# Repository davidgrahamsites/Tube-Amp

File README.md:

# Renegade Tube Amp

KiCad engineering project for an original six-tube amplifier with solid-state spring reverb.

Two separate builds are tracked in Git:

| Branch | Build |
|---|---|
| `electric-guitar-amp` | Original electric-guitar amplifier and spring reverb |
| `acoustic-guitar-amp` | Acoustic-specific input buffer and speaker/crossover development |

For the acoustic build, start with [ACOUSTIC_HANDOFF.md](ACOUSTIC_HANDOFF.md). Read [BUILD_VARIANT.md](BUILD_VARIANT.md) to identify the checked-out build. Read [PROJECT_STATUS.md](PROJECT_STATUS.md) for actual completed checks and unresolved work. Neither branch is a construction release.

## Project map

- [Workspace contract](CONTEXT.md)
- [Current material catalog](brain/catalog/WORKSPACE.md)
- [Requirements and handoff](Renegade_Codex_Handoff.md)
- [Selected component BOM](engineering/component-selection/selected-engineering-bom.csv)
- [Current 600R-1 schematic](engineering/whole-amp/reverb-600/cad/Renegade_220V_Reverb.kicad_sch)
- [Four-board engineering draft](engineering/whole-amp/pcb-measured-r/CONTEXT.md)
- [Measured-resistance simulation and PCB review](engineering/whole-amp/reverb-600/review/measured-resistance-results-2026-11-20.md)
- [Received-cabinet fit evidence](engineering/whole-amp/mechanical/CONTEXT.md)

Historical designs and failed/limited simulations are retained as evidence. Native KiCad factories marked with overwrite guards must not be rerun over later manual edits. Supplier PDFs, source artwork and third-party models retain their original ownership and licensing.

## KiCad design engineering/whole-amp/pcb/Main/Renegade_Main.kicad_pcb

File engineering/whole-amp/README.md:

# Whole-amplifier PCB development — v0.5

**Development only. Not build-ready or released for fabrication.** The original amplifier and v0.4 files are preserved. This revision extends PCB coverage to Main, Power and Control alongside the existing Reverb board. Socket-local grid/screen resistors and cathode sense resistors remain directly at the valve sockets; transformers, valves, panel parts and protective earth remain chassis mounted.

## Current artifacts
- `integrated/Renegade_220V_Reverb.kicad_sch` and `integrated/Renegade-v0.5-development.pdf`: separate integrated development schematic; pin partitions match v0.4.
- `bom-development.csv` and `build-plan.md`: assembly register and staged build/test plan, with unresolved purchase parts explicitly marked.
- `harness-terminals.csv`: terminal-to-net list from saved boards.
- `board-plan.json`: component-to-assembly register, provisional envelopes and footprints.
- `pcb/Main`, `pcb/Power`, `pcb/Control`: editable native board projects and assembly connectivity schematics. All three are routed, with zero native DRC, unconnected and schematic parity issues in the final saved checks. The preserved Reverb project is included in `pcb/Reverb`. This is a development revision, not a fabrication release.
- `validation/pin-partition.json`: native schematic-to-board pad/net mapping checks.
- `validation/*-drc.json`: latest native reports; failures remain visible.
- `simulation/`: reproducible full signal-path and supply stress fixtures, results, models and failure logs.
- `evidence/`: manufacturer documents and supplier contact record.

## Supplier inquiry
Sent and verified in Mail Sent on November 11 at 06:22 America/Los_Angeles, from the user-selected admin@goodgaryapps.com to mable@mableaudio.com. Cabinet choice unchanged. Internal dimensions, Shanghai availability/quote and exact spring-tank documentation requested. No order, attachments or design upload.

## Engineering limits still to close
1. Engineering review of all board placements, return paths, decoupling, heat and coupling. Main/Power were regrouped by circuit section; Control in particular still needs decoupling/thermal placement review. Routing completion is not an analog layout review.
2. Repeat native checks after any engineering changes. Main/Power/Control currently have clean assembly ERC and PCB DRC/parity reports; the integrated schematic retains the documented PE/GND alias warning. Board previews were rendered and inspected.
3. Exact remaining parts, HV standby and fuse coordination, isolated LV transformer and heatsink selection; procurement evidence in China.
4. Full amplifier model qualification: generic valve/ideal magnetics assumptions, overdrive screen stress, solid-state dry-path headroom and transient convergence.
5. Supplier-confirmed internal cabinet geometry and actual component envelopes before chassis/panel fabrication drawings. Current board sizes are provisional and not fit claims.
6. Reviewed grounding, harness, test/bring-up plan and subsequent physical fit/thermal/energized measurements.

No Gerbers are released from this revision. The previous reverb-only package is also an engineering draft, not authorization to manufacture the complete amplifier.

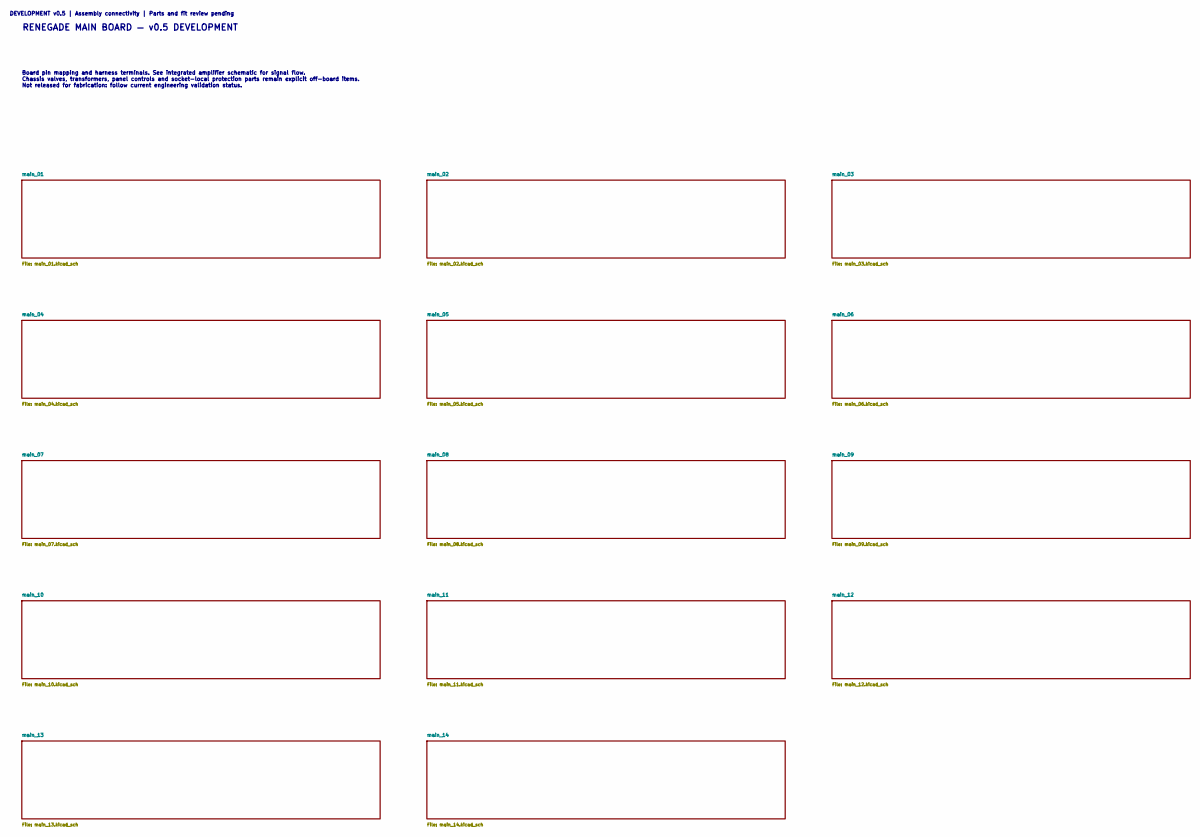
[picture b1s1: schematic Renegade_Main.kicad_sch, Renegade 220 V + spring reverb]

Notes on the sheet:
RENEGADE MAIN BOARD — v0.5 DEVELOPMENT
Board pin mapping and harness terminals. See integrated amplifier schematic for signal flow. Chassis valves, transformers, panel controls and socket-local protection parts remain explicit off-board items. Not released for fabrication: follow current engineering validation status.
DEVELOPMENT v0.5 | Assembly connectivity | Parts and fit review pending

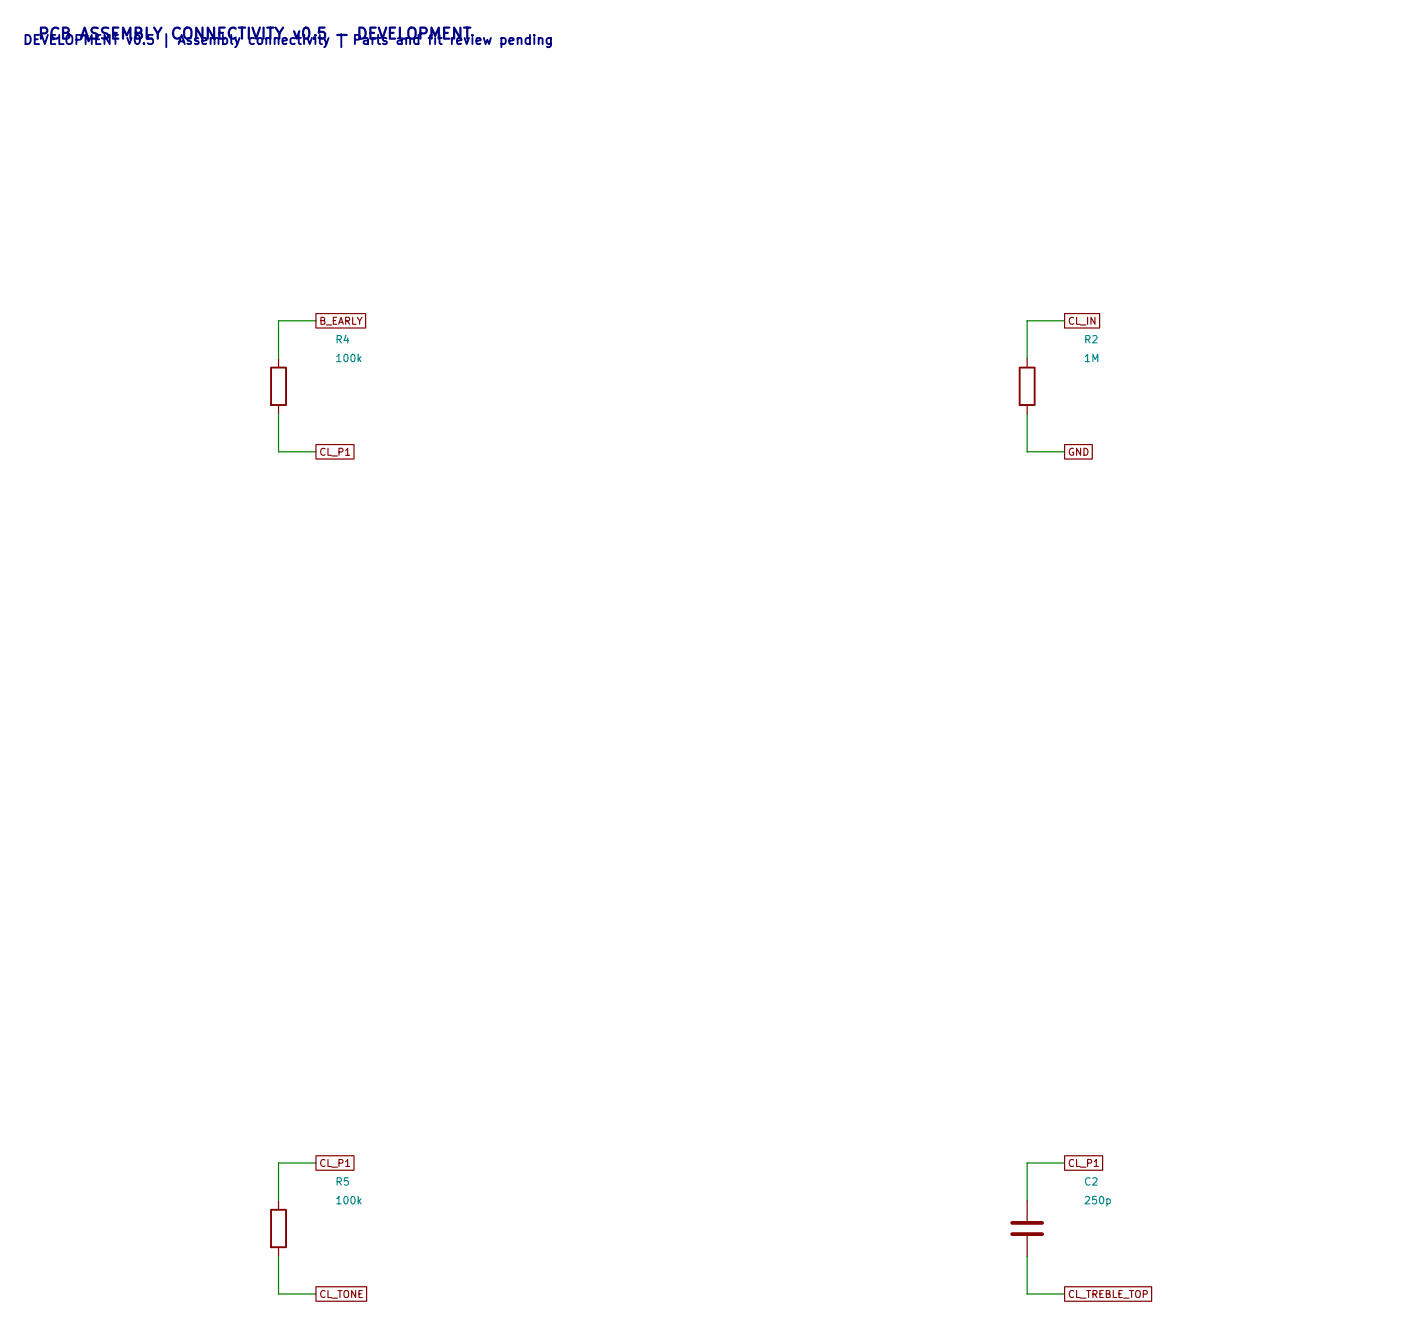
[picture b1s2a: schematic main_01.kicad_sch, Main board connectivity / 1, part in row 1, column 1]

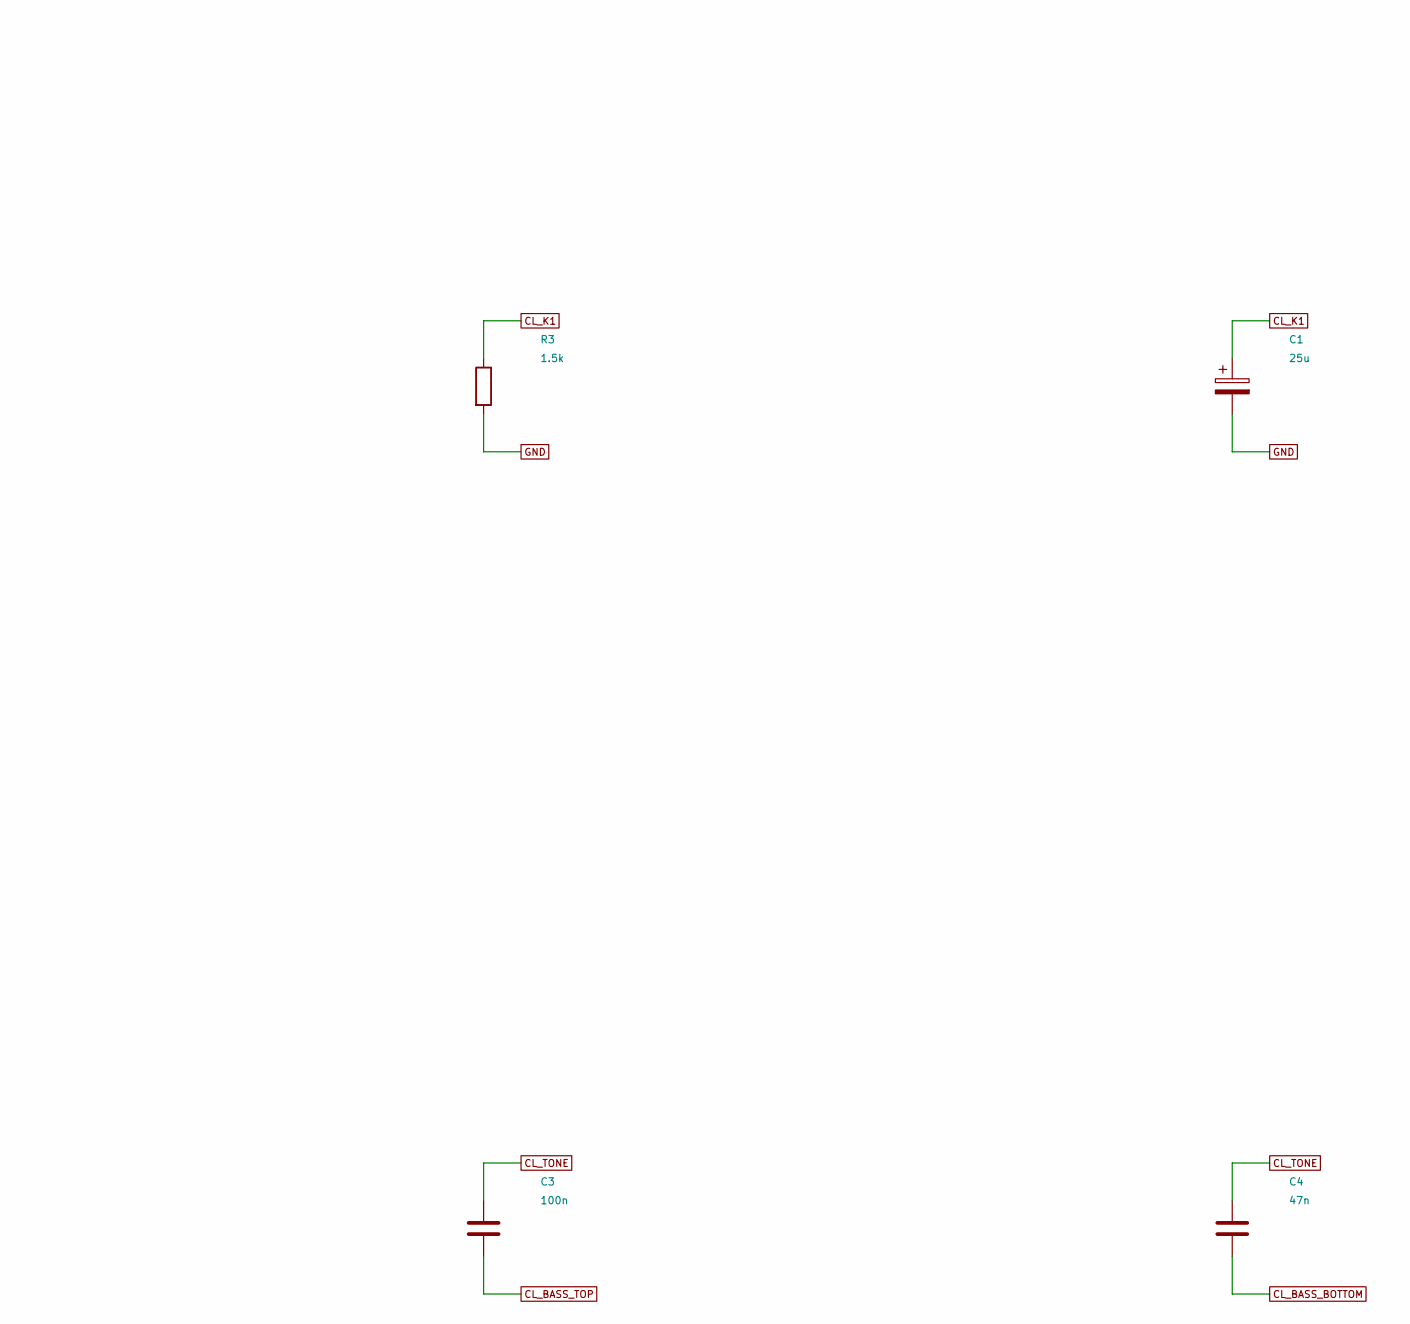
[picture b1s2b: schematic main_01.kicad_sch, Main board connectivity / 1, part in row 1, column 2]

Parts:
C1: 25u; CP_Axial_L25.0mm_D10.0mm_P30.00mm_Horizontal; Rating 50 V
C2: 250p; C_Disc_D7.5mm_W5.0mm_P10.00mm; Rating 630 V film
C3: 100n; C_Rect_L18.0mm_W7.0mm_P15.00mm_FKS3_FKP3; Rating 630 V film
C4: 47n; C_Rect_L18.0mm_W7.0mm_P15.00mm_FKS3_FKP3; Rating 630 V film
R2: 1M; R_Axial_DIN0207_L6.3mm_D2.5mm_P15.24mm_Horizontal; Rating 0.5 W minimum; exact part pending
R3: 1.5k; R_Axial_DIN0207_L6.3mm_D2.5mm_P15.24mm_Horizontal; Rating 0.5 W minimum; exact part pending
R4, R5: 100k; R_Axial_DIN0207_L6.3mm_D2.5mm_P15.24mm_Horizontal; Rating 0.5 W minimum; exact part pending

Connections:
B_EARLY: R4.1; also elsewhere on the board
CL_BASS_BOTTOM: C4.2; also elsewhere on the board
CL_BASS_TOP: C3.2; also elsewhere on the board
CL_IN: R2.1; also elsewhere on the board
CL_K1: C1.1, R3.1; also elsewhere on the board
CL_P1: C2.1, R4.2, R5.1; also elsewhere on the board
CL_TONE: C3.1, C4.1, R5.2
CL_TREBLE_TOP: C2.2; also elsewhere on the board
GND: C1.2, R2.2, R3.2; also elsewhere on the board

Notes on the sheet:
PCB ASSEMBLY CONNECTIVITY v0.5 — DEVELOPMENT
DEVELOPMENT v0.5 | Assembly connectivity | Parts and fit review pending

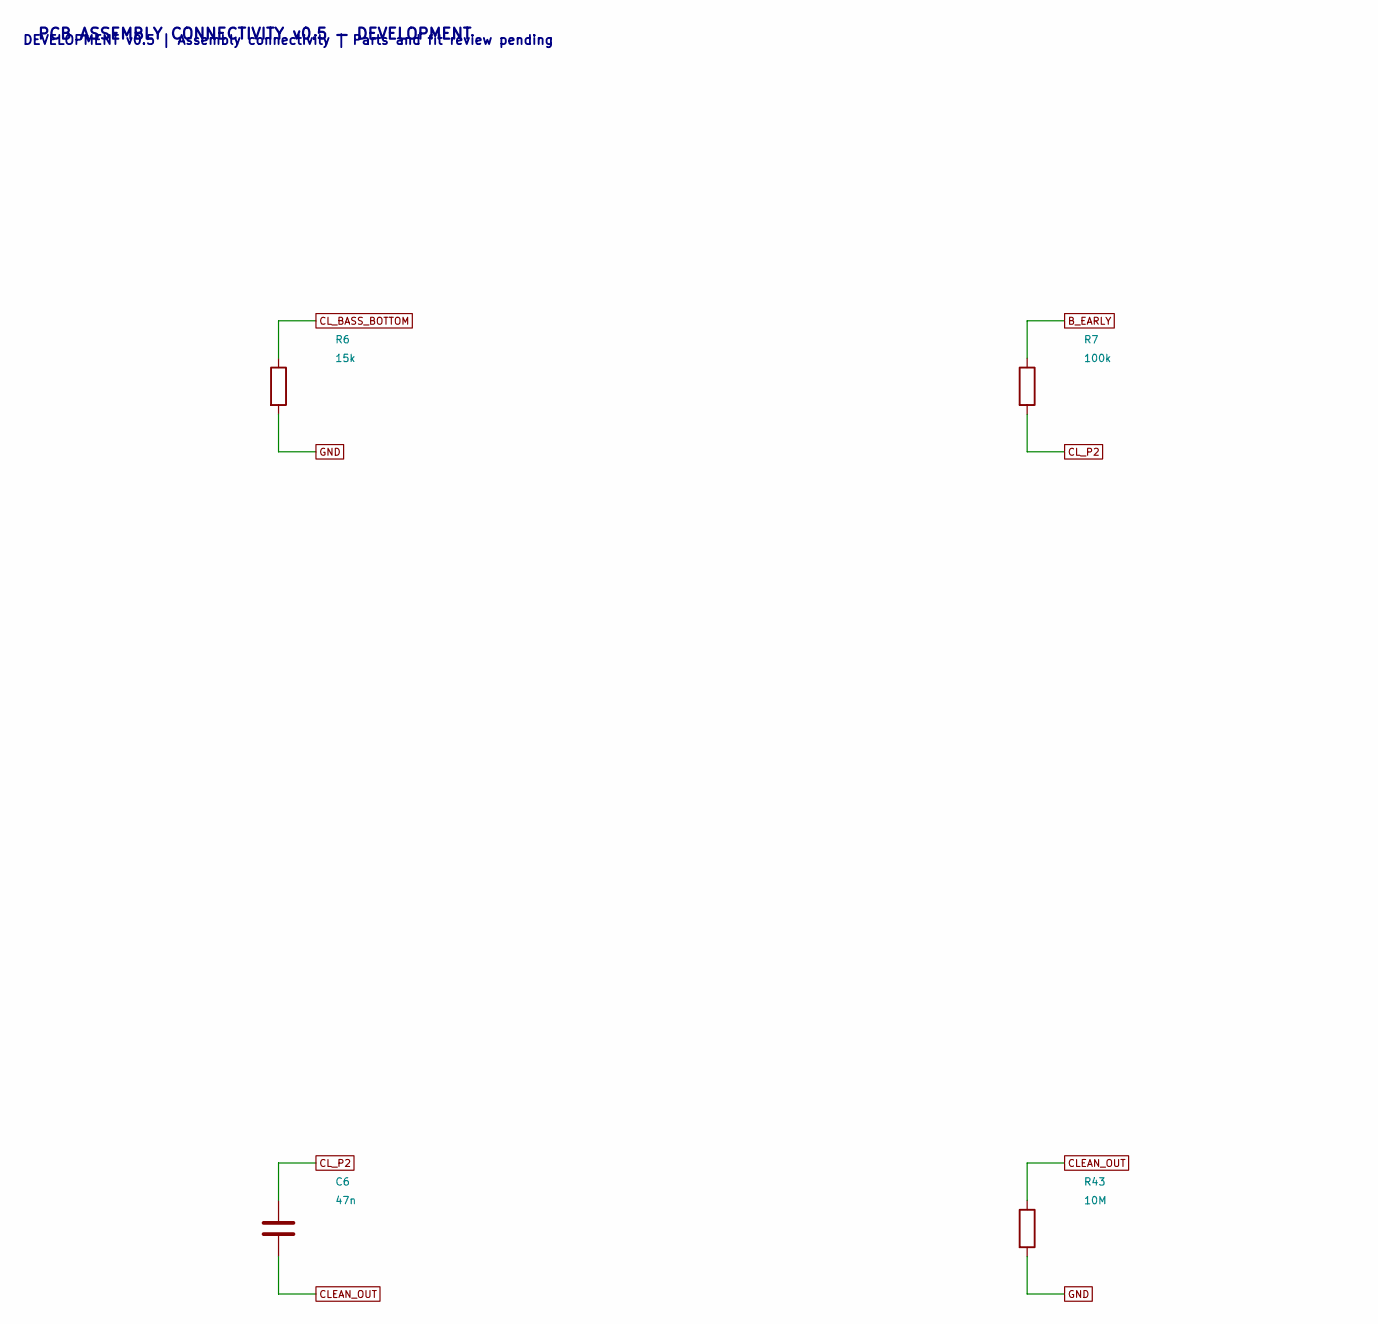
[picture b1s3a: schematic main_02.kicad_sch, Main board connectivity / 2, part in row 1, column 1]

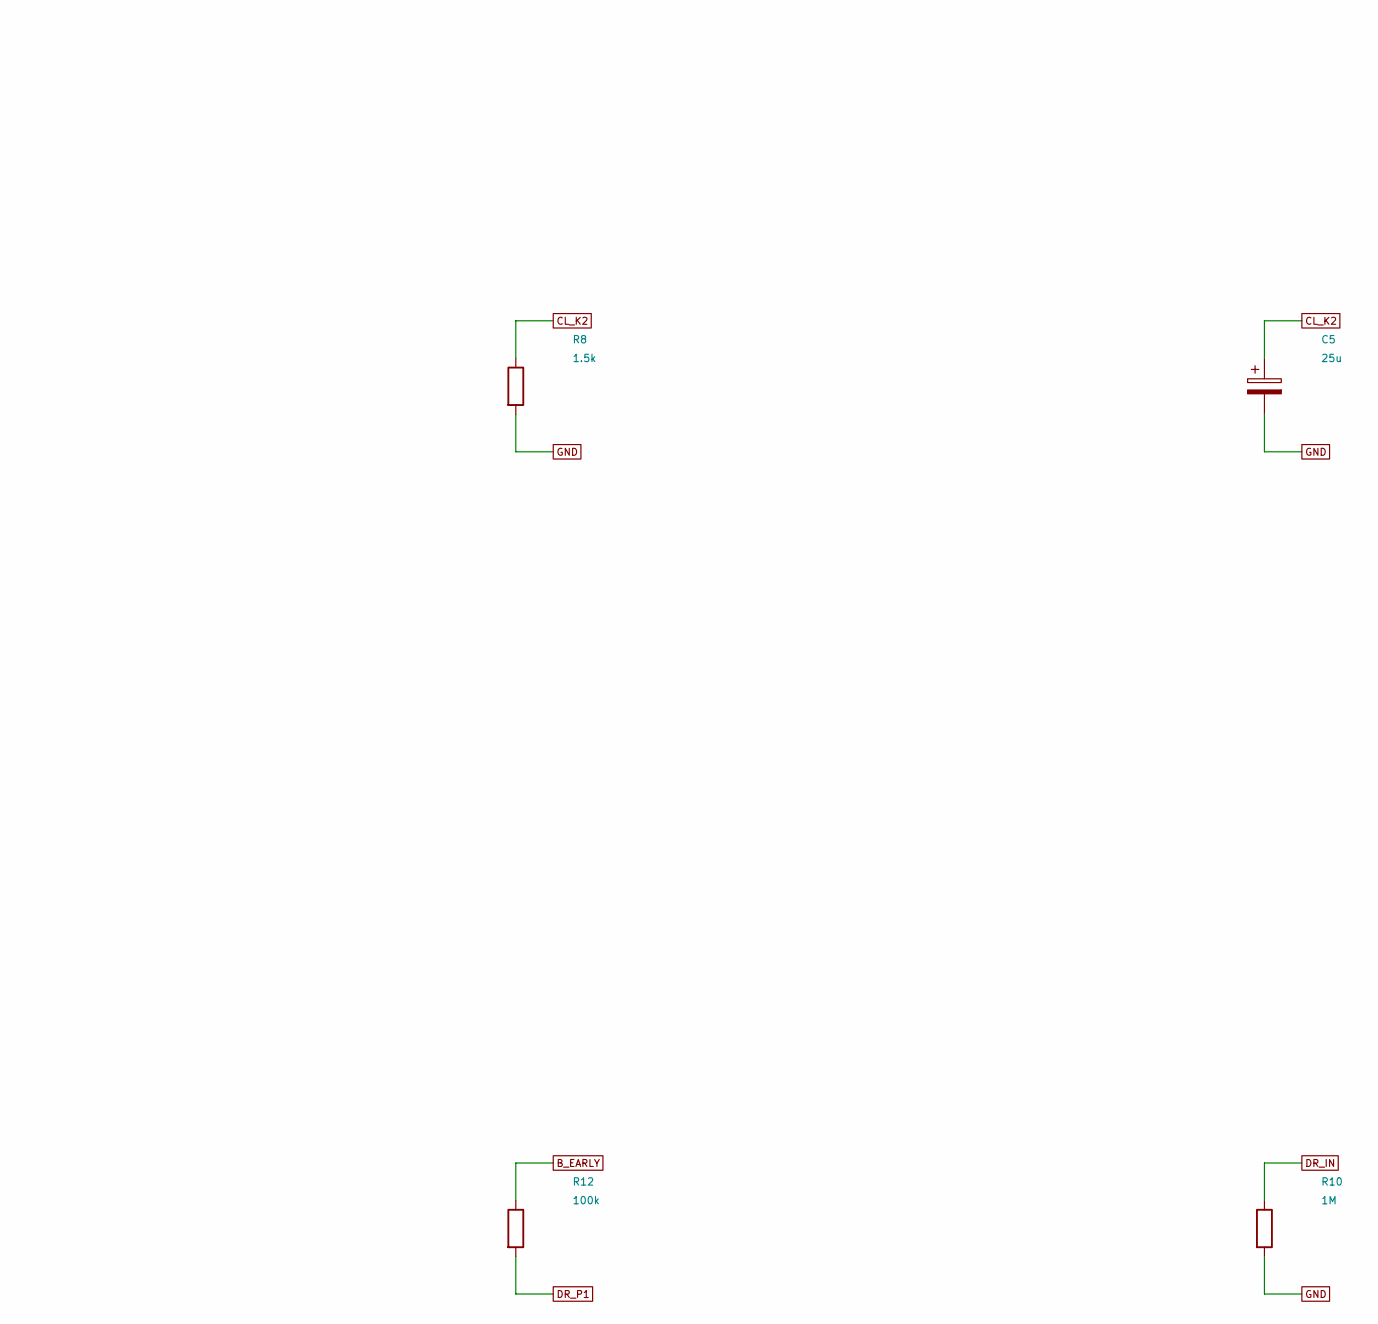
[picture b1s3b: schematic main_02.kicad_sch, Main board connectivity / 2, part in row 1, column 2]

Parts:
C5: 25u; CP_Axial_L25.0mm_D10.0mm_P30.00mm_Horizontal; Rating 50 V
C6: 47n; C_Rect_L18.0mm_W7.0mm_P15.00mm_FKS3_FKP3; Rating 630 V film
R6: 15k; R_Axial_DIN0207_L6.3mm_D2.5mm_P15.24mm_Horizontal; Rating 0.5 W minimum; exact part pending
R7, R12: 100k; R_Axial_DIN0207_L6.3mm_D2.5mm_P15.24mm_Horizontal; Rating 0.5 W minimum; exact part pending
R8: 1.5k; R_Axial_DIN0207_L6.3mm_D2.5mm_P15.24mm_Horizontal; Rating 0.5 W minimum; exact part pending
R10: 1M; R_Axial_DIN0207_L6.3mm_D2.5mm_P15.24mm_Horizontal; Rating 0.5 W minimum; exact part pending
R43: 10M; R_Axial_DIN0207_L6.3mm_D2.5mm_P15.24mm_Horizontal; Rating 0.5 W minimum; exact part pending

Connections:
B_EARLY: R7.1, R12.1; also elsewhere on the board
CLEAN_OUT: C6.2, R43.1; also elsewhere on the board
CL_BASS_BOTTOM: R6.1; also elsewhere on the board
CL_K2: C5.1, R8.1; also elsewhere on the board
CL_P2: C6.1, R7.2; also elsewhere on the board
DR_IN: R10.1; also elsewhere on the board
DR_P1: R12.2; also elsewhere on the board
GND: C5.2, R6.2, R8.2, R10.2, R43.2; also elsewhere on the board

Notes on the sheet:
PCB ASSEMBLY CONNECTIVITY v0.5 — DEVELOPMENT
DEVELOPMENT v0.5 | Assembly connectivity | Parts and fit review pending

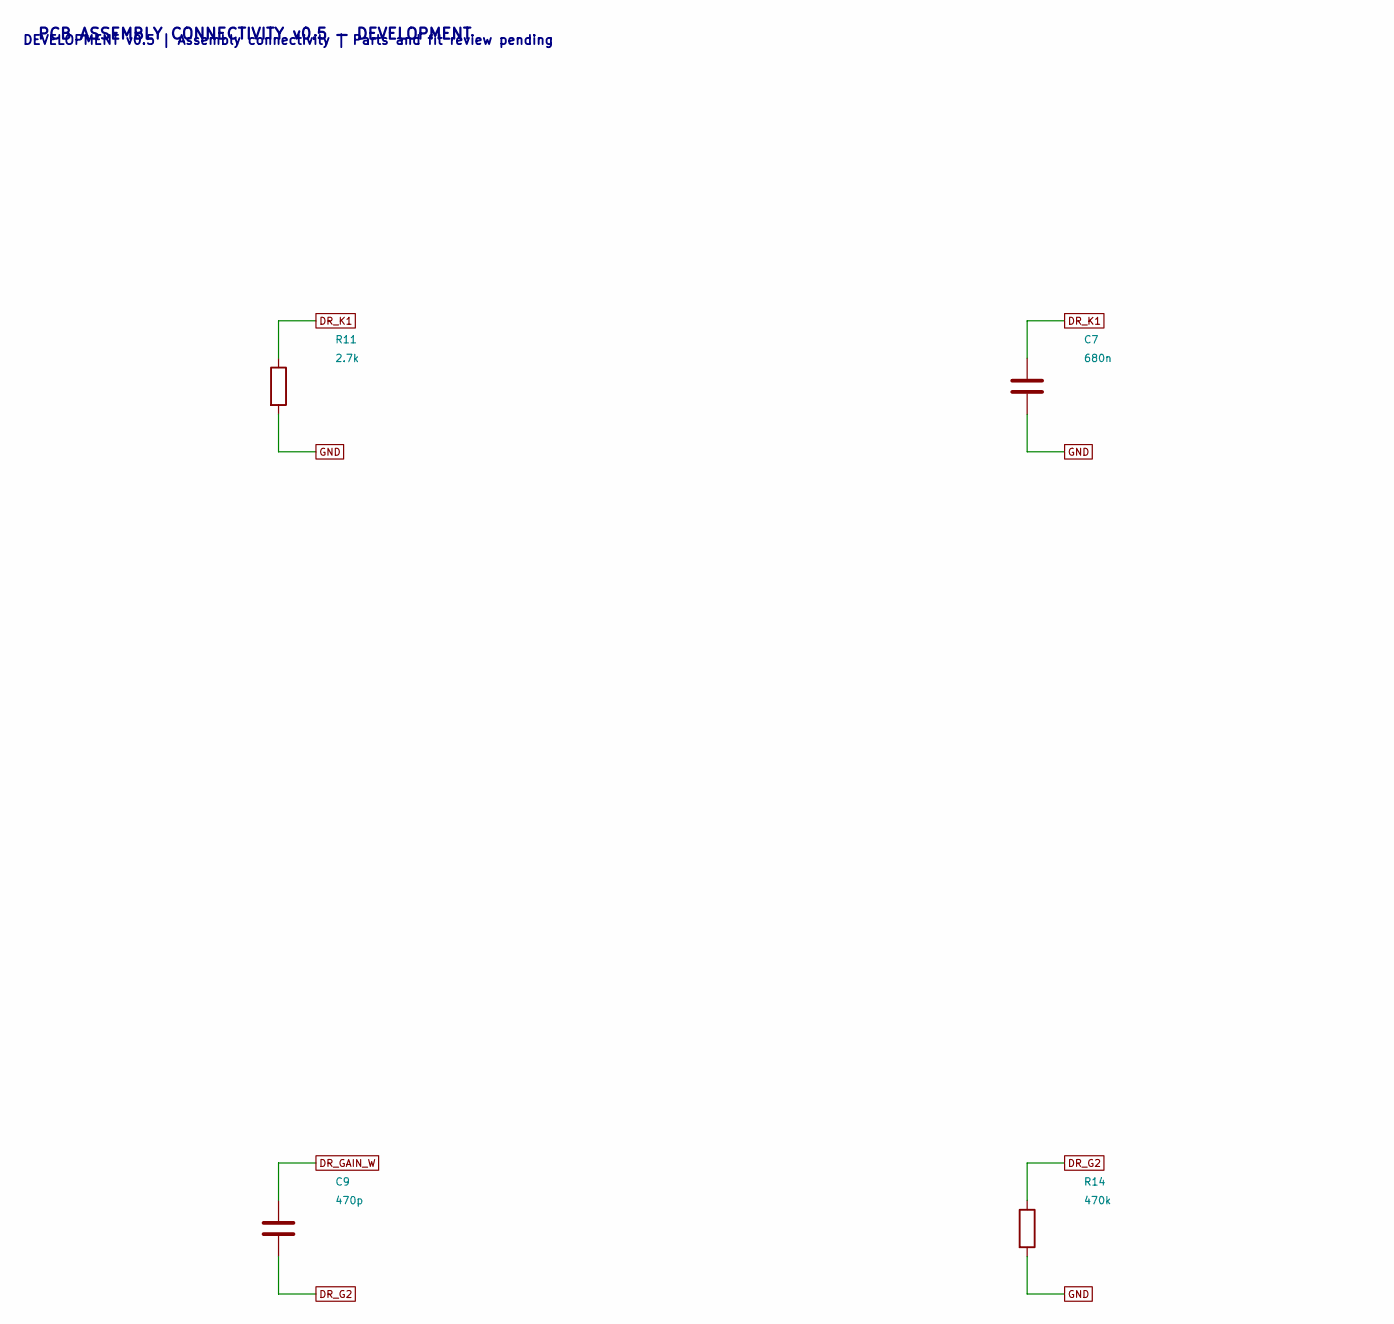
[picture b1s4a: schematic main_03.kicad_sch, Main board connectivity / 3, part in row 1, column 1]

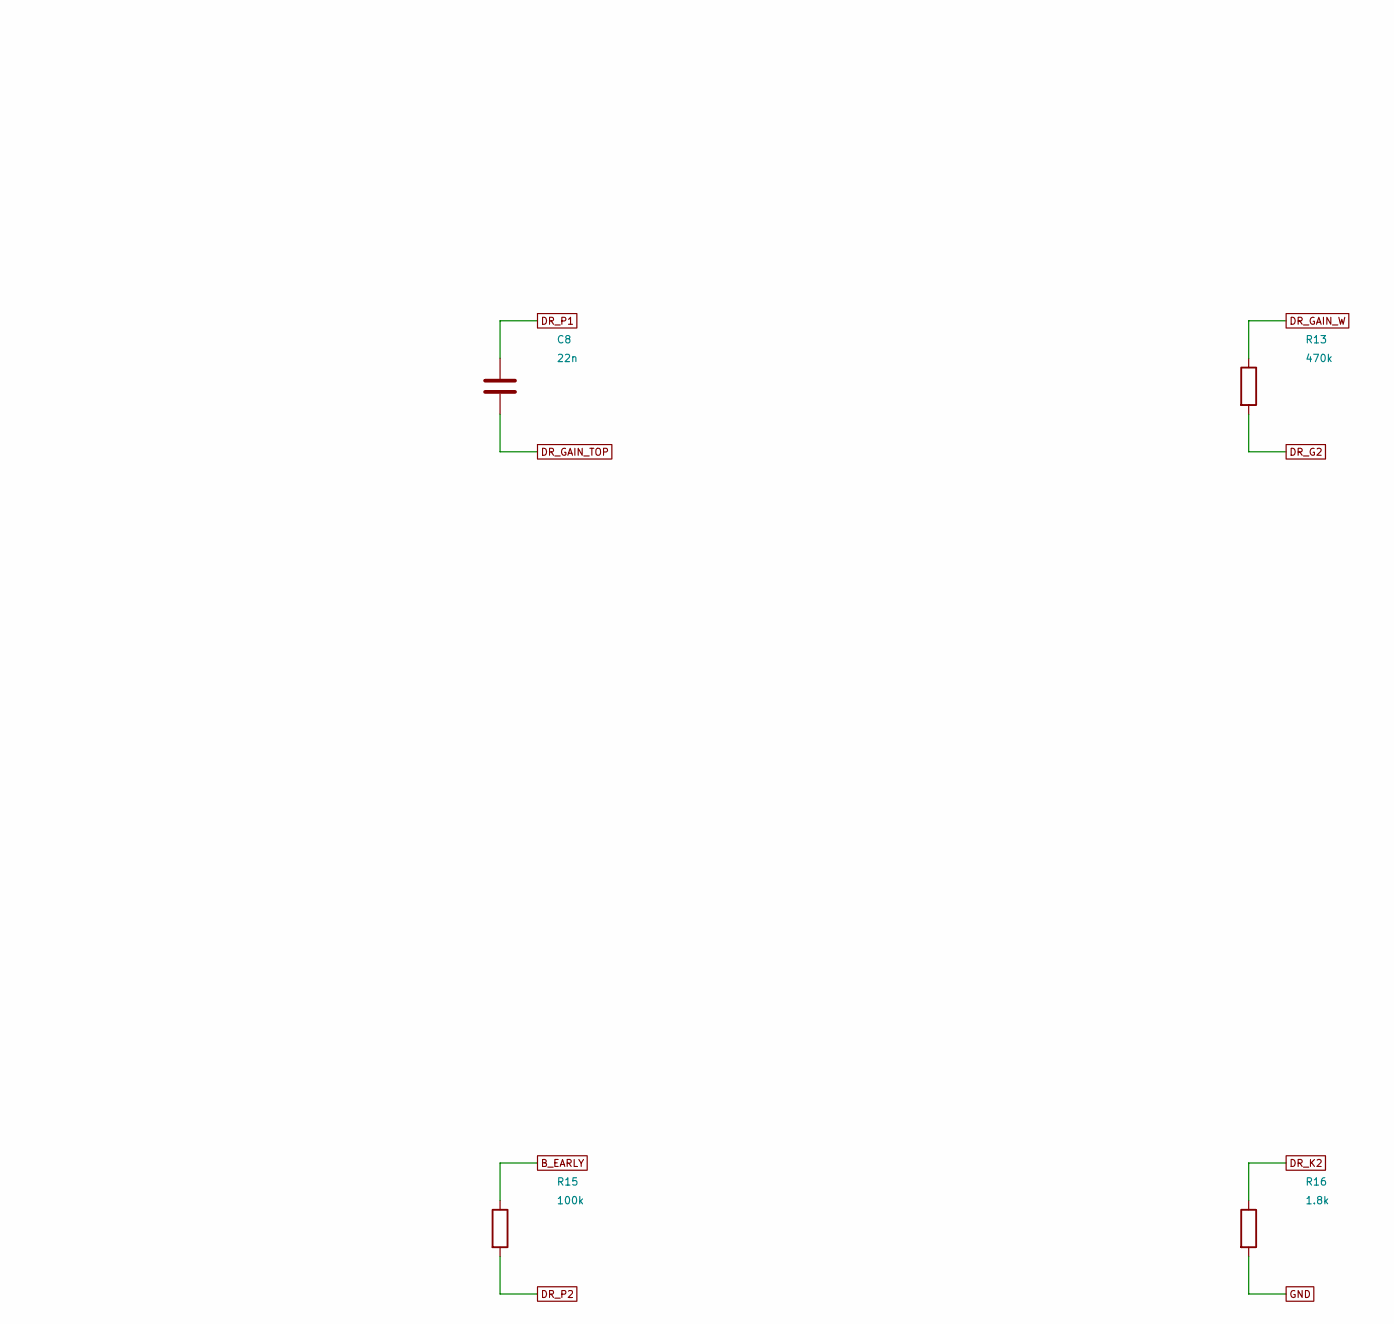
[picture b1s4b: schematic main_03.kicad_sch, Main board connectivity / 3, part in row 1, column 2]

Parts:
C7: 680n; C_Rect_L7.2mm_W5.0mm_P5.00mm; Rating 50 V film
C8: 22n; C_Rect_L18.0mm_W7.0mm_P15.00mm_FKS3_FKP3; Rating 630 V film
C9: 470p; C_Disc_D7.5mm_W5.0mm_P10.00mm; Rating 630 V film
R11: 2.7k; R_Axial_DIN0207_L6.3mm_D2.5mm_P15.24mm_Horizontal; Rating 0.5 W minimum; exact part pending
R13, R14: 470k; R_Axial_DIN0207_L6.3mm_D2.5mm_P15.24mm_Horizontal; Rating 0.5 W minimum; exact part pending
R15: 100k; R_Axial_DIN0207_L6.3mm_D2.5mm_P15.24mm_Horizontal; Rating 0.5 W minimum; exact part pending
R16: 1.8k; R_Axial_DIN0207_L6.3mm_D2.5mm_P15.24mm_Horizontal; Rating 0.5 W minimum; exact part pending

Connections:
B_EARLY: R15.1; also elsewhere on the board
DR_G2: C9.2, R13.2, R14.1; also elsewhere on the board
DR_GAIN_TOP: C8.2; also elsewhere on the board
DR_GAIN_W: C9.1, R13.1; also elsewhere on the board
DR_K1: C7.1, R11.1; also elsewhere on the board
DR_K2: R16.1; also elsewhere on the board
DR_P1: C8.1; also elsewhere on the board
DR_P2: R15.2; also elsewhere on the board
GND: C7.2, R11.2, R14.2, R16.2; also elsewhere on the board

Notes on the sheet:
PCB ASSEMBLY CONNECTIVITY v0.5 — DEVELOPMENT
DEVELOPMENT v0.5 | Assembly connectivity | Parts and fit review pending

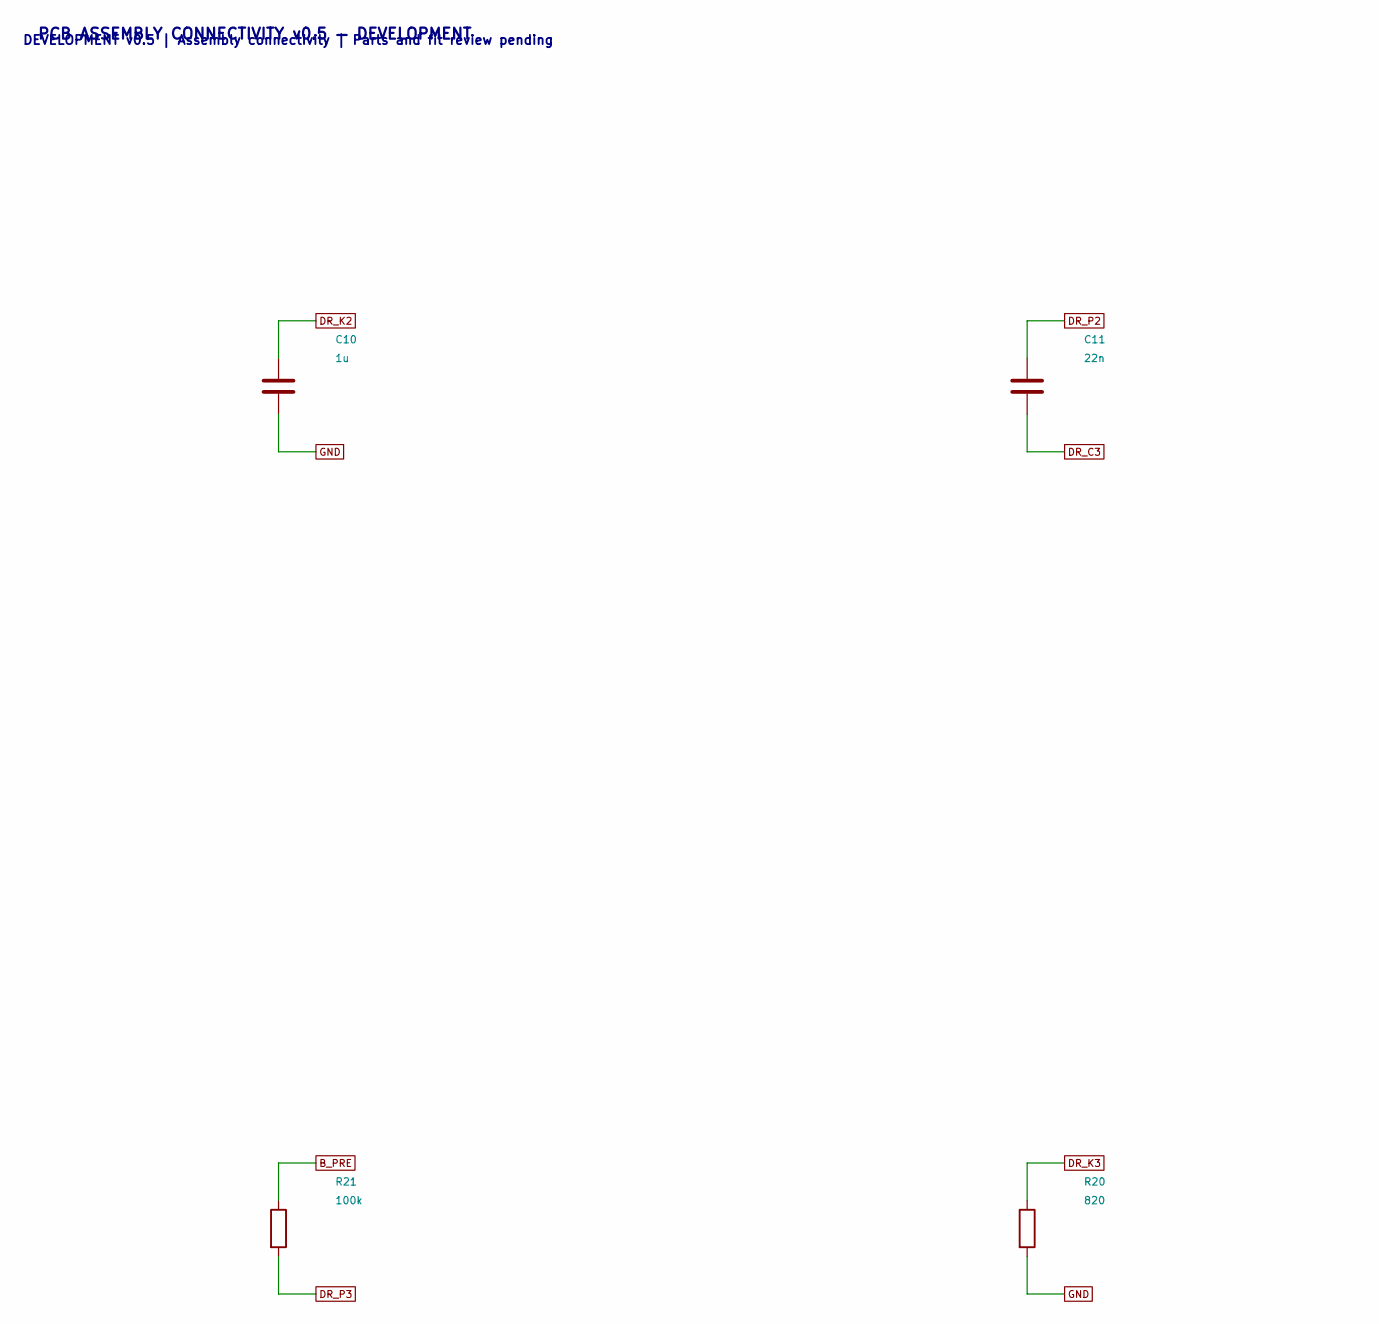
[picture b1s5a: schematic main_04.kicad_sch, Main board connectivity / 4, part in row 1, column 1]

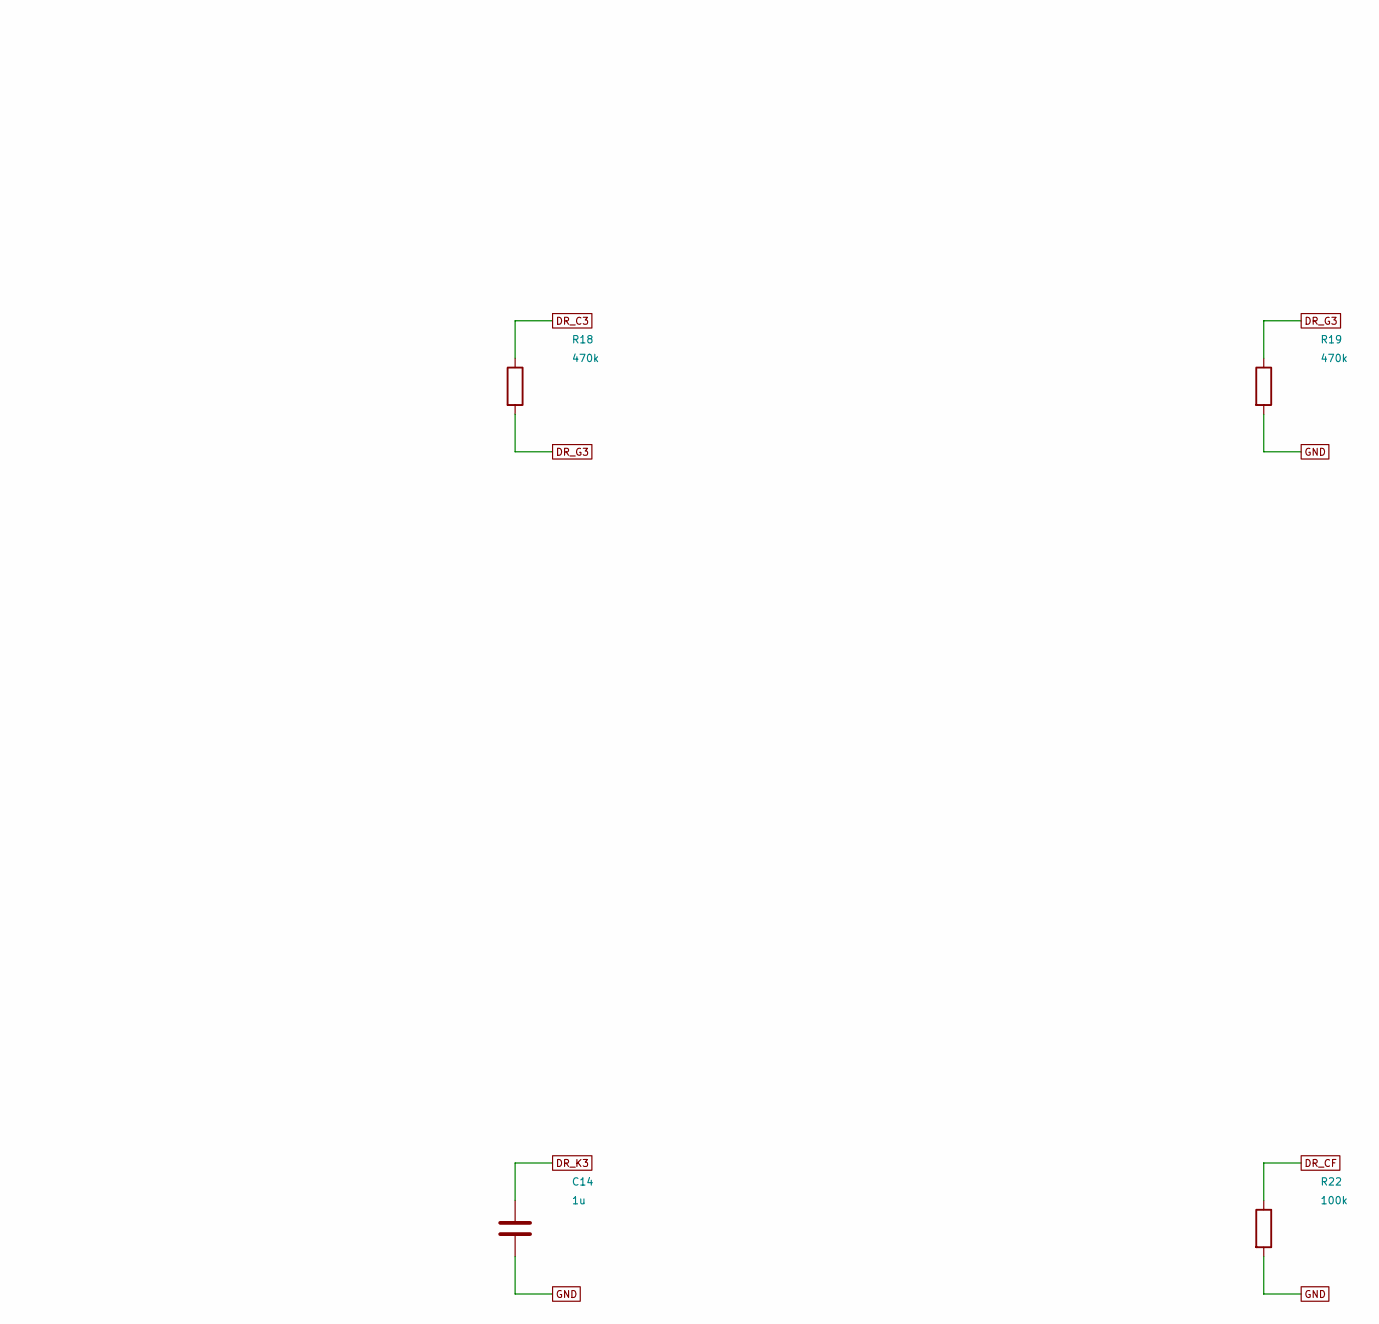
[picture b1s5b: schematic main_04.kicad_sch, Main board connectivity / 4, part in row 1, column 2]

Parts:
C10, C14: 1u; C_Rect_L7.2mm_W5.0mm_P5.00mm; Rating 50 V
C11: 22n; C_Rect_L18.0mm_W7.0mm_P15.00mm_FKS3_FKP3; Rating 630 V film
R18, R19: 470k; R_Axial_DIN0207_L6.3mm_D2.5mm_P15.24mm_Horizontal; Rating 0.5 W minimum; exact part pending
R20: 820; R_Axial_DIN0207_L6.3mm_D2.5mm_P15.24mm_Horizontal; Rating 0.5 W minimum; exact part pending
R21: 100k; R_Axial_DIN0207_L6.3mm_D2.5mm_P15.24mm_Horizontal; Rating 0.5 W minimum; exact part pending
R22: 100k; R_Axial_DIN0207_L6.3mm_D2.5mm_P15.24mm_Horizontal; Rating 2 W minimum; Vk stress pending

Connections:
B_PRE: R21.1; also elsewhere on the board
DR_C3: C11.2, R18.1
DR_CF: R22.1; also elsewhere on the board
DR_G3: R18.2, R19.1; also elsewhere on the board
DR_K2: C10.1; also elsewhere on the board
DR_K3: C14.1, R20.1; also elsewhere on the board
DR_P2: C11.1; also elsewhere on the board
DR_P3: R21.2; also elsewhere on the board
GND: C10.2, C14.2, R19.2, R20.2, R22.2; also elsewhere on the board

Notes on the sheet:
PCB ASSEMBLY CONNECTIVITY v0.5 — DEVELOPMENT
DEVELOPMENT v0.5 | Assembly connectivity | Parts and fit review pending
